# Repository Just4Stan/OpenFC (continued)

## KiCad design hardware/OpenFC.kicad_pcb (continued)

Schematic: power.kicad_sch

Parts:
C2, C16: 22uF; C_0402_1005Metric; LCSC C105226
C32, C33, C36, C39: 100n; C_0201_0603Metric; LCSC C76939
C35, C37: 4.7uF 50v; C_0805_2012Metric; LCSC C98192
C38, C40, C48: 22uF; C_0603_1608Metric; LCSC C2762594
D1, D4, D5, D7: LED_1_Green; LED_0603_1608Metric; LCSC C2994781
D3, D21: RB161QS-40_C28646385; SOD-882_L1.0-W0.6-RD; LCSC Part C28646385
L3, L4: XRTC303020D4R7MBCA; IND-SMD_L3.0-W3.0_AFE303020S; LCSC Part C39846837
Q1: DMN1150UFB-7B; DFN-3L_L1.0-W0.6-P0.65-BR; LCSC Part C459538
R4: 30R; C_0201_0603Metric; LCSC C778391
R7, R14, R16: 100k; C_0201_0603Metric; LCSC C270364
R8: 39k; C_0201_0603Metric; LCSC C473053
R12, R15: 200R; C_0201_0603Metric; LCSC C270359
R19: 10k; C_0201_0603Metric; LCSC C473048
R28: 5.23k; C_0201_0603Metric; LCSC C851767
R29: 470R; C_0201_0603Metric; LCSC C473464
R31: 13.7k; C_0201_0603Metric; LCSC C138175
U6, U7: LMR51420YFDDCR; SOT-23-6_L2.9-W1.6-P0.95-LS2.9-BL; LCSC Part C7296200
U13: TPS746-3.3DRV; WSON-6-1EP_2x2mm_P0.65mm_EP1x1.6mm; LCSC C2868202
U21: NCV8187AMT180TAG; WDFN-6_L2.0-W2.0-P0.65-BL-EP; LCSC Part C893189
U33: TPS2116DRLR; SOT-583-8_L2.1-W1.6-P0.50-LS1.6-BL; LCSC Part C3235557

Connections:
+1.8V_GYRO: C2.1, U21.5 (SNS), U21.6 (OUT); also elsewhere on the board
+3.3V: C16.1, R4.1, U13.1 (OUT); also elsewhere on the board
+5V: C32.1, C33.1, C48.1, D3.1 (C), R12.1, R19.2, U13.4 (EN), U13.6 (IN), U21.1 (IN), U21.2 (EN), U33.2 (VOUT), U33.7 (VOUT); also elsewhere on the board
+5V_BUCK: C40.1, D3.2 (A), L4.2, R7.2, R15.1, R16.2, U33.3 (VIN1), U33.5 (MODE)
+5V_USB: U33.6 (VIN2); also elsewhere on the board
+12V: C38.1, L3.2, R14.2, R29.1; also elsewhere on the board
+BATT: C35.1, C37.1, D21.1 (C), U6.3 (VIN), U7.3 (VIN), U7.5 (EN); also elsewhere on the board
/POWER/1.8V_PG: Q1.1 (G), R19.1, U21.4 (PG)
/POWER/10V_ENABLE: U6.5 (EN); also elsewhere on the board
unnamed: D1.2 (A), R15.2
unnamed: D4.2 (A), R4.2
unnamed: D5.2 (A), R29.2
unnamed: D7.2 (A), R12.2
unnamed: D7.1 (K), Q1.3 (D)
unnamed: C36.2, U6.6 (CB)
unnamed: R14.1, R28.1, U6.4 (FB)
unnamed: C36.1, L3.1, U6.2 (SW)
unnamed: C39.2, U7.6 (CB)
unnamed: R16.1, R31.1, U7.4 (FB)
unnamed: C39.1, L4.1, U7.2 (SW)
unnamed: R7.1, R8.1, U33.4 (PR1)

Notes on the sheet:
10V (2A)
3.3V 1A MAIN LDO
FPWM version of the LMR51420YFDDCR for less output ripple at low voltage and more consistency but less efficient
1.8V 150mA LDO (high PSRR)
5V (2A)
5V Power MUX
Switches up to 4A (TPS2117) from +5V_USB or +5V_BUCK to +5V. Prefers buck over USB, threshold voltage is about 3.5V. The threshold voltage is low to prevent accidental switchover to USB during peak consumption (worst case in flight). Emergency diode for if that happens during flight.

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
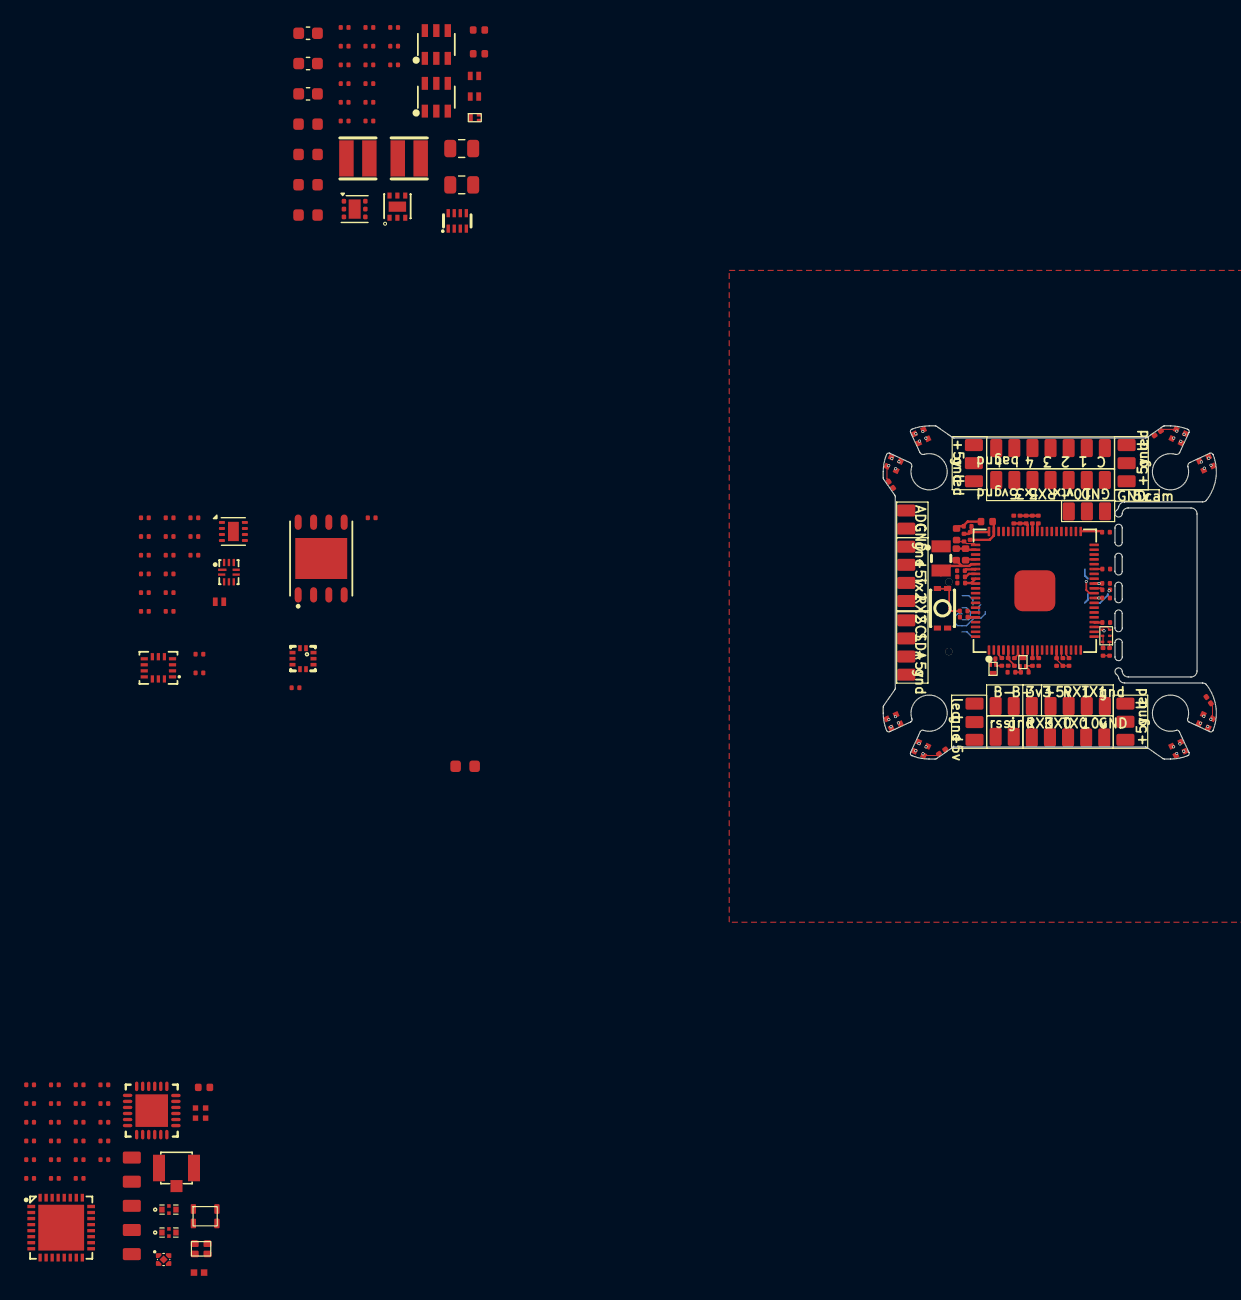
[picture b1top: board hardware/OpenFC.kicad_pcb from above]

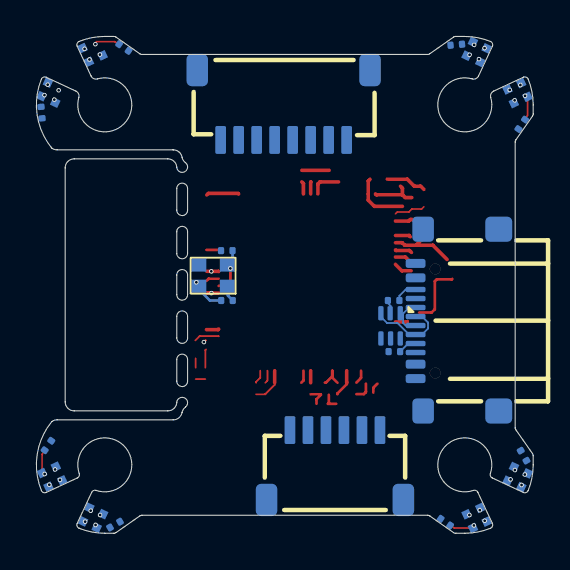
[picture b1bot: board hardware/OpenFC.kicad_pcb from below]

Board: 8 copper layers, 27.6 x 27.6 mm, 233 parts (25 on the bottom side), 130 nets.

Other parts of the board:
J51, J52, J54, J55, J57, J58, J59: 5V; small_pad

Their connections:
+3.3V: J59.1; also elsewhere on the board
+12V: J58.1; also elsewhere on the board
/PADS/ADC2: J52.1; also elsewhere on the board
/PADS/PIOUART1_RX: J57.1; also elsewhere on the board
/PADS/PIOUART1_TX: J55.1; also elsewhere on the board

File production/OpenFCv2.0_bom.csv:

Designator,Footprint,Quantity,Value,LCSC Part #
"C1, C9",0402,2,10nF,C15195
"C11, C111, C12, C13, C14, C18, C19, C2, C32, C34, C41, C45, C46, C47, C49, C5, C50, C51, C52, C53, C54, C55, C56, C57, C58, C60, C61, C62, C63, C64, C65, C70, C72, C75, C76, C78, C79, C8, C80, C81, C82, C83, C84, C85, C86, C87",0402,46,100n,C1525
"C16, C17",0402,2,22uF,C105226
C33,0402,1,1uF,C1525
"C35, C37",0805,2,4.7uF 50v,C98192
"C36, C39",0402,2,100nF,
"C38, C40, C48",0603,3,22uF,C2762594
C43,0402,1,10uF,C105226
C59,0402,1,15p,C441742
"C67, C68, C71, C77",0402,4,4.7uF,C23733
C7,0402,1,470nF,C92361
"C73, C74",0402,2,20p,C441742
"D1, D4, D5, D6, D7",0603,5,LED_1_Green,C2994781
"D21, D3",SOD-882_L1.0-W0.6-RD,2,RB161QS-40_C28646385,C28646385
D8,SOT-23-6_L2.9-W1.6-P0.95-LS2.8-BL,1,USBLC6-2SC6,C7519
"FL1, FL2",FILTER-SMD_4P-L1.0-W0.5-L,2,DEA102700LT-6307A2,C574024
"J1, J10, J11, J12, J13, J14, J15, J16, J17, J18, J19, J2, J20, J21, J22, J23, J24, J25, J26, J27, J28, J29, J3, J30, J31, J32, J33, J34, J35, J36, J38, J39, J4, J40, J42, J43, J44, J45, J46, J47, J48, J49, J5, J50, J51, J52, J53, J54, J55, J56, J57, J6, J7, J8, J9",small_pad,55,5V,
L1,IND-SMD_L2.0-W1.6_AOTA-B201610S3R3-101-T,1,AOTA-B201610S3R3-101-T,C42411119
"L3, L4",IND-SMD_L3.0-W3.0_AFE303020S,2,XRTC303020D4R7MBCA,C39846837
L7,L0402,1,LQG15HS2N0S02D,C18216
OSC1,OSC-SMD_4P-L2.0-W1.6-BL_TXC_7Z,1,OW7EL89CENUNFAYLC-52M,C22434896
P1,CONN-TH_SM08B-SRSS-TB-LF-SN,1,SM08B-SRSS-TB(LF)(SN),C160407
"Q1, Q7",DFN-3L_L1.0-W0.6-P0.65-BR,2,DMN1150UFB-7B,C459538
"R1, R3, R40, R47, R54, R6, R9",0402,7,10k,C2909316
R10,0402,1,100R,
"R11, R38",0402,2,10k,
"R12, R15, R55",0402,3,200R,C25087
R13,0402,1,1k,C106235
"R14, R16, R46, R5, R7",0402,5,100k,C60491
R17,0402,1,100k,
R18,0402,1,75R,
R2,0402,1,1M,
"R22, R4, R48, R49, R56",0402,5,30R,C138007
"R27, R32",0402,2,33R,
R28,0402,1,5.23k,C2684530
R29,0402,1,470,C114877
"R30, R33",0402,2,1k,
R31,0402,1,13.7k,C2933072
R35,0402,1,150k,
R39,0402,1,4.7k,
R42,0402,1,6.8k,C105872
R43,0402,1,6.8k,C2906876
"R51, R52",0402,2,5.1k,C105872
R53,0402,1,1k,C2909316
R8,0402,1,39k,C137995
RF1,IPEX-SMD_3P-L2.6-W2.6-LS3.0,1,CONUFL001-SMD-T,C22418213
TP1,TestPoint_Pad_D1.0mm,1,TestPoint,
U1,CONN-SMD_SM06B-SRSS-TB-LF-SN,1,SM06B-SRSS-TB(LF)(SN),C160405
"U10, U39",TDFN-6_L1.0-W1.0-P0.35-BL,2,74LVC1G66,
U12,UDFN-4_L1.0-W1.0-P0.65-TL,1,WL9005D4-33,C5357206
U13,WSON-6-1EP_2x2mm_P0.65mm_EP1x1.6mm,1,TPS746-3.3DRV,C2868202
U14,LGA-14_L3.0-W2.5-P0.50-BR,1,LSM6DSV16XTR,C5267406
"U15, U16, U17, U18, U19, U22, U23, U24, U25, U26, U27, U28, U29, U3, U4, U5, U8",LED-SMD_4P-L1.0-W1.0-TL_XL-1010RGBC-WS2812B,17,XL-1010RGBC-WS2812B,C5349953
U2,QFN-32_L5.0-W5.0-P0.50-TL-EP3.7,1,ESP32-C3FH4,C2858491
U20,QFN-24_L4.0-W4.0-P0.50-TL-EP2.6,1,SX1281IMLTRT,C2151551
U21,WDFN-6_L2.0-W2.0-P0.65-BL-EP,1,NCV8187AMT180TAG,C893189
U30,SENSORM-SMD_BMP388,1,BMP388,C779278
U33,SOT-583-8_L2.1-W1.6-P0.50-LS1.6-BL,1,TPS2116DRLR,C3235557
U35,UMLP-10_L1.8-W1.4-P0.40-BL,1,FSUSB42UMX,C11145
U36,QFN-80_L10.0-W10.0-P0.40-TL-EP3.4,1,RP2354B_C39843328,C39843328
U37,WSON-8-1EP_2x2mm_P0.5mm_EP0.9x1.6mm,1,TLV9062IDSGR,C2058009
U38,WSON-8-1EP_2x2mm_P0.5mm_EP0.9x1.6mm,1,LM393LVDSGR,C3658410
U41,SW-SMD_4P-L3.0-W2.0-P0.85-LS3.5,1,TS2306A 240GF MSM 9_C2976675,C2976675
U42,SC-70-6_L2.0-W1.3-P0.65-LS2.1-BL,1,TXU0101DCKR,C5217868
"U6, U7",SOT-23-6_L2.9-W1.6-P0.95-LS2.9-BL,2,LMR51420YDDCR,C5383002
U9,WSON-8_L6.0-W5.0-P1.27-BL-EP,1,BY25Q128ASWIG(R),C394872
USB1,USB-TYPE-C-SMD_TYPE-C-16P-QTWT,1,TYPE-C 16P QTWT,C5187472
X1,CRYSTAL-SMD_4P-L2.5-W2.0-BL-A,1,XTM25012000JT00351001,C37635340

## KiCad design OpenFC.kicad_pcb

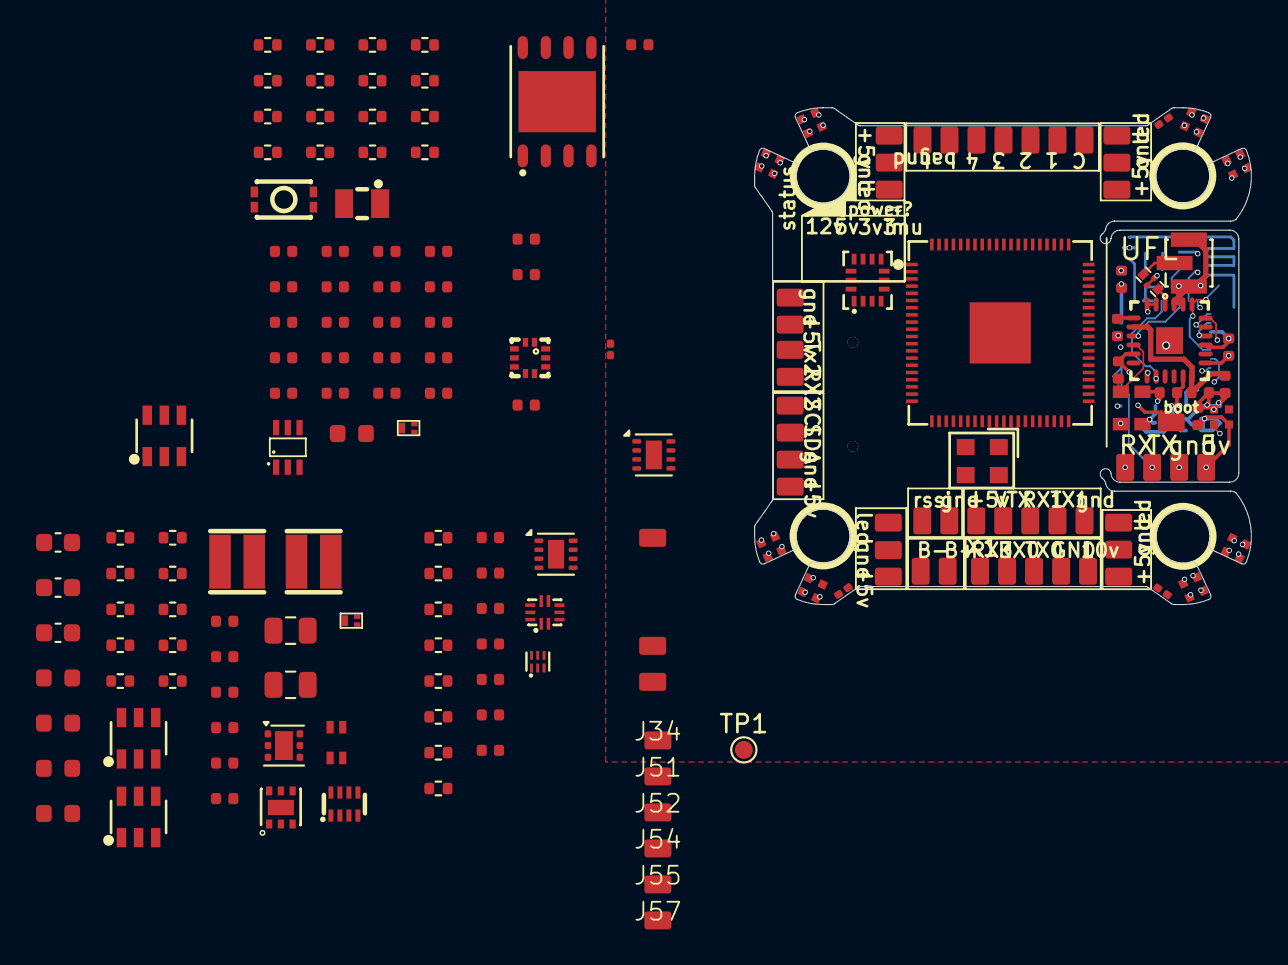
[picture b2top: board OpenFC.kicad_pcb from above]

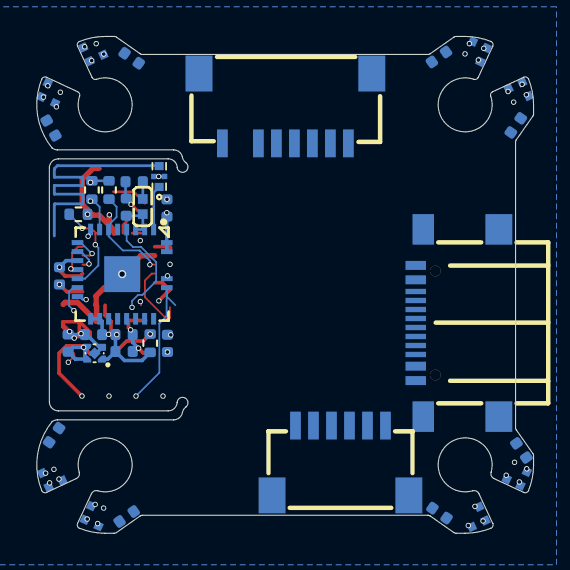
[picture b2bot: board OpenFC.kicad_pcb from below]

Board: 8 copper layers, 27.6 x 27.6 mm, 222 parts (36 on the bottom side), 113 nets.

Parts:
C1, C9: 10nF; C_0402_1005Metric
C5, C8, C11, C12, C13, C14, C18, C19, C32, C34, C41, C45, C46, C47, C49, C50, C51, C52, C53, C54, C55, C56, C57, C58, C60, C61, C62, C63, C64, C65, C66, C70, C72, C75, C76, C78, C79, C80, C81, C82, C83, C84, C85, C86, C87, C111: 100n; C_0402_1005Metric
C7: 470nF; C_0402_1005Metric
C16, C17: 22uF; C_0402_1005Metric
C33: 1uF; C_0402_1005Metric
C35, C37: 4.7uF 50v; C_0805_2012Metric
C36, C39: 100nF; C_0402_1005Metric
C38, C40, C48: 22uF; C_0603_1608Metric
C43: 10uF; C_0402_1005Metric
C59: 15p; C_0402_1005Metric
C67, C68, C71, C77: 4.7uF; C_0402_1005Metric
C73, C74: 20p; C_0402_1005Metric
D1, D4, D5, D6, D7: LED_1_Green; LED_0603_1608Metric
D3, D21: RB161QS-40_C28646385; SOD-882_L1.0-W0.6-RD
D8: USBLC6-2SC6; SOT-23-6_L2.9-W1.6-P0.95-LS2.8-BL
FL1, FL2: DEA102700LT-6307A2; FILTER-SMD_4P-L1.0-W0.5-L
J1, J2, J3, J4, J5, J6, J7, J8, J9, J10, J11, J12, J13, J14, J15, J16, J17, J18, J19, J20, J21, J22, J23, J24, J25, J26, J27, J28, J29, J30, J31, J32, J33, J34, J35, J36, J38, J39, J40, J42, J43, J44, J45, J46, J47, J48, J49, J50, J51, J52, J53, J54, J55, J56, J57: 5V; small_pad
JP1, JP2, JP3, JP4: SolderJumper_2_Open; MouseBite-Slot-Jumper_0201
L1: AOTA-B201610S3R3-101-T; IND-SMD_L2.0-W1.6_AOTA-B201610S3R3-101-T
L3, L4: XRTC303020D4R7MBCA; IND-SMD_L3.0-W3.0_AFE303020S
L7: LQG15HS2N0S02D; L0402
OSC1: OW7EL89CENUNFAYLC-52M; OSC-SMD_4P-L2.0-W1.6-BL_TXC_7Z
P1: SM08B-SRSS-TB(LF)(SN); CONN-TH_SM08B-SRSS-TB-LF-SN
Q1, Q7: DMN1150UFB-7B; DFN-3L_L1.0-W0.6-P0.65-BR
R1, R3, R6, R9, R38, R40, R47, R54: 10k; R_0402_1005Metric
R2: 1M; R_0402_1005Metric
R4, R22, R48, R49, R56: 30R; R_0402_1005Metric
R5, R7, R14, R16, R46: 100k; R_0402_1005Metric
R8: 39k; R_0402_1005Metric
R12, R15, R55: 200R; R_0402_1005Metric
R13, R30, R33, R53: 1k; R_0402_1005Metric
R27, R32: 33R; R_0402_1005Metric
R28: 5.23k; R_0402_1005Metric
R29: 470; R_0402_1005Metric
R31: 13.7k; R_0402_1005Metric
R35: 150k; R_0402_1005Metric
R39: 4.7k; R_0402_1005Metric
R42, R43: 6.8k; R_0402_1005Metric
R51, R52: 5.1k; R_0402_1005Metric
RF1: CONUFL001-SMD-T; IPEX-SMD_3P-L2.6-W2.6-LS3.0
TP1: TestPoint; TestPoint_Pad_D1.0mm
U1: SM06B-SRSS-TB(LF)(SN); CONN-SMD_SM06B-SRSS-TB-LF-SN
U2: ESP32-C3FH4; QFN-32_L5.0-W5.0-P0.50-TL-EP3.7
U3, U4, U5, U8, U15, U16, U17, U18, U19, U22, U23, U24, U25, U26, U27, U28, U29: XL-1010RGBC-WS2812B; LED-SMD_4P-L1.0-W1.0-TL_XL-1010RGBC-WS2812B
U6, U7: LMR51420YDDCR; SOT-23-6_L2.9-W1.6-P0.95-LS2.9-BL
U9: BY25Q128ASWIG(R); WSON-8_L6.0-W5.0-P1.27-BL-EP
U12: WL9005D4-33; UDFN-4_L1.0-W1.0-P0.65-TL
U13: TPS746-3.3DRV; WSON-6-1EP_2x2mm_P0.65mm_EP1x1.6mm
U14: LSM6DSV16XTR; LGA-14_L3.0-W2.5-P0.50-BR
U20: SX1281IMLTRT; QFN-24_L4.0-W4.0-P0.50-TL-EP2.6
U21: NCV8187AMT180TAG; WDFN-6_L2.0-W2.0-P0.65-BL-EP
U30: BMP388; SENSORM-SMD_BMP388
U33: TPS2116DRLR; SOT-583-8_L2.1-W1.6-P0.50-LS1.6-BL
U35: FSUSB42UMX; UMLP-10_L1.8-W1.4-P0.40-BL
U36: RP2354B_C39843328; QFN-80_L10.0-W10.0-P0.40-TL-EP3.4
U37: TLV9062IDSGR; WSON-8-1EP_2x2mm_P0.5mm_EP0.9x1.6mm
U38: LM393LVDSGR; WSON-8-1EP_2x2mm_P0.5mm_EP0.9x1.6mm
U39: 74LVC1G66; TDFN-6_L1.0-W1.0-P0.35-BL
U41: TS2306A 240GF MSM 9_C2976675; SW-SMD_4P-L3.0-W2.0-P0.85-LS3.5
U42: TXU0101DCKR; SC-70-6_L2.0-W1.3-P0.65-LS2.1-BL
USB1: TYPE-C 16P QTWT; USB-TYPE-C-SMD_TYPE-C-16P-QTWT
X1: XTM25012000JT00351001; CRYSTAL-SMD_4P-L2.5-W2.0-BL-A

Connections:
+1.1V: C68.1, C72.1, C75.1, C76.1, L1.1, U36.10 (DVDD), U36.32 (DVDD), U36.51 (DVDD), U36.65 (VREG_FB)
+1.8V_GYRO: C41.1, C43.1, Q1.1 (G), U14.8 (Vdd), U21.5 (SNS), U21.6 (OUT)
+3.3V: C16.1, C34.1, C45.1, C49.1, C61.1, C62.1, C65.1, C67.1, C78.1, C79.1, C80.1, C81.1, C82.1, C83.1, C84.1, C85.1, C86.1, C111.1, R4.1, R35.2, R39.2, R42.1, R43.1, R54.1, R55.1, R56.1, U9.3 (~WP), U9.7 (~HOLD), U9.8 (VCC), U13.1 (OUT), U14.5 (Vdd_IO), U30.1 (VDDIO), U30.6 (CSB), U30.10 (VDD), U35.9 (VCC), U36.5 (IOVDD), U36.15 (IOVDD), U36.24 (IOVDD), U36.29 (IOVDD), U36.41 (IOVDD), U36.50 (IOVDD), U36.60 (IOVDD), U36.64 (VREG_VIN), U36.68 (USB_OTP_VDD), U36.69 (QSPI_IOVDD), U36.76 (IOVDD), U37.8 (V+), U38.8 (V+), U39.6 (VCC), U42.1 (VCCA)
+3.3V_ELRS: C5.1, C8.1, C17.1, C52.1, C53.1, C54.1, C55.1, C56.1, C60.1, OSC1.4 (VDD), R1.1, R3.1, R6.1, U2.11 (VDD3P3_RTC), U2.17 (VDD3P3_CPU), U2.18 (VDD_SPI), U2.31 (VDDA), U2.32 (VDDA), U12.1 (VOUT), U20.11 (VBAT_IO), U20.15 (VBAT)
+5V: C11.1, C12.1, C13.1, C14.1, C18.1, C19.1, C32.1, C33.1, C46.1, C47.1, C48.1, C57.1, C58.1, C87.2, D3.1 (C), J6.1, J13.1, J16.1, J19.1, J22.1, J26.1, J34.1, J39.1, J48.1, J49.1, J53.1, R12.1, U3.2 (VDD), U4.2 (VDD), U5.2 (VDD), U8.2 (VDD), U12.3 (EN), U12.4 (VIN), U13.4 (EN), U13.6 (IN), U15.2 (VDD), U16.2 (VDD), U17.2 (VDD), U18.2 (VDD), U19.2 (VDD), U21.1 (IN), U21.2 (EN), U22.2 (VDD), U23.2 (VDD), U24.2 (VDD), U25.2 (VDD), U26.2 (VDD), U27.2 (VDD), U28.2 (VDD), U29.2 (VDD), U33.2 (VOUT), U33.7 (VOUT), U42.5 (OE), U42.6 (VCCB)
+5V_BUCK: C40.1, D3.2 (A), L4.2, R7.1, R15.1, R16.2, U33.3 (VIN1), U33.5 (MODE)
+5V_USB: D8.5, U33.6 (VIN2), USB1.A4 (VBUS), USB1.A9 (VBUS)
+12V: C38.1, J28.1, L3.2, R14.2, R29.1, U1.1
+BATT: C35.1, C37.1, D21.1 (C), J2.1, P1.2, R46.1, U6.3 (VIN), U6.5 (EN), U7.3 (VIN), U7.5 (EN)
/BLACKBOX/BB_CS: U9.1 (~CS), U36.57 (GPIO46_ADC6)
/COMPASS/I2C_SCL: R43.2, U36.16 (GPIO16)
/COMPASS/I2C_SDA: R42.2, U36.17 (GPIO17)
/ELRS/BUSY: U2.8 (GPIO3), U20.7 (BUSY)
/ELRS/CS: R9.1, U2.13 (MTDO), U20.19 (NSS_CTS)
/ELRS/DIO: U2.4 (XTAL_32K_P), U20.8 (DIO1)
/ELRS/ESP8285_EN: R3.2, U2.7 (CHIP_EN)
/ELRS/ESP_BOOT0: J12.1, R1.2, U2.15 (GPIO9)
/ELRS/MISO: U2.10 (MTDI), U20.16 (MISO_TX)
/ELRS/MOSI: U2.9 (MTMS), U20.17 (MOSI_RX)
/ELRS/RGBLED: U2.14 (GPIO8), U19.4 (DIN)
/ELRS/RST: R6.2, U2.6 (GPIO2), U20.3 (NRESET)
/ELRS/SCK: U2.12 (MTCK), U20.18 (SCK_RTSN)
/IMU/GYRO_CS: U14.12 (CS), U36.3 (GPIO6)
/IMU/GYRO_INT: U14.4 (INT1), U36.6 (GPIO8)
/LED: J15.1, J18.1, J21.1, J30.1
/LED's/LED_STRIP: JP1.1 (A), JP2.1 (A), JP3.1 (A), JP4.1 (A)
/OSD/OSD_CLAMP_EN: U36.43 (GPIO34), U39.4
/OSD/OSD_PIXSEL: U35.10 (SEL), U36.42 (GPIO33)
/OSD/OSD_SYNC_RAW: R39.1, U36.40 (GPIO32), U38.1
/OSD/OSD_VWHITE_PWM: R30.1, U36.44 (GPIO35)
/OSD/VIDEO_IN: C63.1, J32.1
/OSD/VIDEO_OUT: C66.2, J33.1
/OSD/VID_AC: C63.2, R2.1, R27.1
/OSD/VID_BUF: U35.6 (HSD2-), U35.7 (HSD2+), U37.1, U37.2 (-)
/OSD/VID_CLAMP: R27.2, R33.1, U37.3 (+), U39.1
/OSD/VID_MUX_OUT: R32.1, U35.1 (D+), U35.2 (D-)
/OSD/VWHITE_BUF: U35.4 (HSD1-), U35.5 (HSD1+), U37.6 (-), U37.7
/OSD/VWHITE_FILT: C64.2, R30.2, U37.5 (+)
/PADS/ADC2: J52.1, U36.58 (GPIO47_ADC7)
/PADS/BUZZER-: J40.1, Q7.3 (D)
/PADS/CURRENT: J27.1, P1.8, U36.49 (GPIO40_ADC0)
/PADS/DIGITAL_RX: J36.1, U1.4, U36.78 (GPIO1)
/PADS/DIGITAL_TX: J35.1, U1.3, U36.77 (GPIO0)
/PADS/M1: J3.1, P1.6, U36.36 (GPIO28)
/PADS/M2: J4.1, P1.5, U36.37 (GPIO29)
/PADS/M3: J24.1, P1.4, U36.38 (GPIO30)
/PADS/M4: J25.1, P1.3, U36.39 (GPIO31)
/PADS/PIOUART0_RX: J45.1, U36.26 (GPIO25)
/PADS/PIOUART0_TX: J46.1, U36.25 (GPIO24)
/PADS/RSSI: J56.1, U36.56 (GPIO45_ADC5)
/PADS/SBUS: J38.1, U1.6
/RP2350A/ADC_VBAT: C70.1, R46.2, R47.2, U36.52 (GPIO41_ADC1)
/RP2350A/BEEPER: R13.1, U36.13 (GPIO14)
/RP2350A/D+: D8.6, R49.2
/RP2350A/D+_C: D8.1, USB1.A6 (DP1), USB1.B6 (DP2)
/RP2350A/D-: D8.4, R48.2
/RP2350A/D-_C: D8.3, USB1.A7 (DN1), USB1.B7 (DN2)
/RP2350A/DBG_OSD: TP1.1, U36.45 (GPIO36)
/RP2350A/LED0: R22.2, U36.11 (GPIO12)
/RP2350A/LED_STRIP_L: U36.23 (GPIO23), U42.3 (A)
/RP2350A/XIN: C74.2, U36.30 (XIN), X1.1
/RP2350A/XOUT: C73.2, R53.2, U36.31 (XOUT)
/UART1_RX: J11.1, J44.1, U2.28 (U0TXD), U36.21 (GPIO21)
/UART1_TX: J10.1, J43.1, U2.27 (U0RXD), U36.22 (GPIO22)
GND: C1.1, C5.2, C7.2, C8.2, C9.1, C11.2, C12.2, C13.2, C14.2, C16.2, C17.2, C18.2, C19.2, C32.2, C33.2, C34.2, C35.2, C37.2, C38.2, C40.2, C41.2, C43.2, C45.2, C46.2, C47.2, C48.2, C49.2, C50.2, C51.2, C52.2, C53.2, C54.2, C55.2, C56.2, C57.2, C58.2, C59.1, C60.2, C61.2, C62.2, C64.1, C65.2, C67.2, C68.2, C70.2, C71.2, C72.2, C73.1, C74.1, C75.2, C76.2, C77.2, C78.2, C79.2, C80.2, C81.2, C82.2, C83.2, C84.2, C85.2, C86.2, C87.1, C111.2, D1.1 (K), D4.1 (K), D5.1 (K), D6.1 (K), D8.2, D21.2 (A), FL1.2 (GND), FL1.4 (GND), FL2.2 (GND), FL2.4 (GND), J1.1, J5.1, J9.1, J14.1, J17.1, J20.1, J23.1, J29.1, J31.1, J42.1, J47.1, J50.1, J51.1, J54.1, OSC1.1 (GND), OSC1.2 (GND), P1.1, P1.9, P1.10, Q1.2 (S), Q7.2 (S), R2.2, R5.1, R8.2, R9.2, R28.2, R31.2, R38.1, R40.1, R47.1, R51.1, R52.1, RF1.2, RF1.3, U1.2, U1.5, U1.7, U1.8, U2.33 (EP), U3.3 (GND), U4.3 (GND), U5.3 (GND), U6.1 (GND), U7.1 (GND), U8.3 (GND), U9.4 (VSS), U9.9 (EP), U12.2 (GND), U12.5 (SGND), U13.3 (GND), U13.5 (PG), U13.7 (EP), U14.2 (SDx/AH1/Qvar1), U14.3 (SCx/AH2/Qvar2), U14.6 (GND), U14.7 (GND), U15.3 (GND), U16.3 (GND), U17.3 (GND), U18.3 (GND), U19.3 (GND), U20.5 (GND), U20.13 (GND), U20.20 (GND), U20.21 (GND), U20.23 (GND), U20.24 (GND), U20.25 (EP), U21.3 (GND), U21.7 (EP), U22.3 (GND), U23.3 (GND), U24.3 (GND), U25.3 (GND), U26.3 (GND), U27.3 (GND), U28.3 (GND), U29.3 (GND), U30.3 (VSS), U30.5 (SDO), U30.8 (VSS), U30.9 (VSS), U33.1 (GND), U35.3 (GND), U35.8 (~OE), U36.62 (VREG_PGND), U36.81 (GND), U37.4 (V-), U38.4 (V-), U38.5 (+), U38.6 (-), U39.2, U39.3 (GND), U42.2 (GND), USB1.0 (EH), USB1.A1 (GND), USB1.A12 (GND), X1.2 (GND), X1.4 (GND)
unnamed: C50.1, L7.2, U2.2 (VDD3P3), U2.3 (VDD3P3)
unnamed: C51.1, L7.1
unnamed: C66.1, R32.2
unnamed: D1.2 (A), R15.2
unnamed: D4.2 (A), R4.2
unnamed: D5.2 (A), R29.2
unnamed: D6.2 (A), R22.1
unnamed: D7.2 (A), R12.2
unnamed: D7.1 (K), Q1.3 (D)
unnamed: FL1.1 (IN), U20.22 (RFIO)
unnamed: FL1.3 (OUT), RF1.1
unnamed: FL2.1 (IN), U2.1 (LNA_IN)
unnamed: JP1.2 (B), U15.4 (DIN)
unnamed: JP2.2 (B), U17.4 (DIN)
unnamed: JP3.2 (B), U5.4 (DIN)
unnamed: JP4.2 (B), U3.4 (DIN)
unnamed: C59.2, OSC1.3 (Out_Put), U20.4 (XTA)
unnamed: Q7.1 (G), R5.2, R13.2
unnamed: R40.2, U41.1
unnamed: R53.1, X1.3
unnamed: C36.2, U6.6 (CB)
unnamed: R14.1, R28.1, U6.4 (FB)
unnamed: C36.1, L3.1, U6.2 (SW)
unnamed: C39.2, U7.6 (CB)
unnamed: R16.1, R31.1, U7.4 (FB)
unnamed: C39.1, L4.1, U7.2 (SW)
unnamed: U15.1 (DOUT), U16.4 (DIN), U26.4 (DIN)
unnamed: U16.1 (DOUT), U27.4 (DIN)
unnamed: U17.1 (DOUT), U18.4 (DIN), U28.4 (DIN)
unnamed: U18.1 (DOUT), U29.4 (DIN)
unnamed: C1.2, C7.1, U20.2 (VDD_IN), U20.12 (DCC_FB)
unnamed: C9.2, U20.1 (VR_PA)
unnamed: U3.1 (DOUT), U4.4 (DIN), U22.4 (DIN)
unnamed: U4.1 (DOUT), U23.4 (DIN)
unnamed: U5.1 (DOUT), U8.4 (DIN), U24.4 (DIN)
unnamed: U8.1 (DOUT), U25.4 (DIN)
unnamed: R7.2, R8.1, U33.4 (PR1)
unnamed: C71.1, R55.2, U36.59 (ADC_AVDD)
unnamed: U36.75 (QSPI_SS), U41.2
unnamed: R54.2, U36.35 (RUN)
unnamed: R48.1, U36.66 (USB_DM)
unnamed: R49.1, U36.67 (USB_DP)
unnamed: C77.1, R56.2, U36.61 (VREG_AVDD)
unnamed: L1.2, U36.63 (VREG_LX)
unnamed: R33.2, U38.3 (+)
unnamed: R35.1, R38.2, U38.2 (-)
unnamed: R51.2, USB1.A5 (CC1)
unnamed: R52.2, USB1.B5 (CC2)

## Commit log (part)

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2026-01-16 Update README to remove sensor specifications
    Removed barometer and magnetometer details from the sensors section.
2026-01-16 Add images to README for better visualization
    Added images to enhance the README documentation.
2026-01-16 First routing
2026-01-17 Revised routing. All logic is routed just need uart and power planes
2026-01-17 almost finished routing
2026-01-17 Final routing
2026-01-17 ESP XTAL routed with 1 via
2026-01-17 fixed gyro power and rp2350 inductor
2026-01-17 added silkscreen graphics
2026-01-17 Add new screenshots to README.md
2026-01-17 as ordered
2026-01-18 Switched to RP2354A and re-routed
2026-01-18 Update README with new features and images
2026-01-19 Added Open-OSD-X and new layout
2026-01-22 Ordered first revision
2026-01-23 Switched to RP2354B for V2 of the FC for more IO. I want to try implement OSD on PIO state machine. I know BF already uses all of them but it should be possible and then later try to combine it witht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
2026-01-30 Cleaned up directory. Ordered first revision of FC (30x30) and cleaned up schematic
2026-01-30 Revise README with updated hardware specifications
    Updated microcontroller and sensor specifications, added details for analog OSD, and revised connectivity information.
2026-01-31 switched to 0201
